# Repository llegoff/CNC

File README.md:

CNC
===

Fraiseuse à commande numérique
------------------------------

SmoothieBox
-----------

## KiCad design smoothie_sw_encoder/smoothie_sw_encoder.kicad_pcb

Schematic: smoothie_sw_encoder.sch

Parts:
P1: CONN_5
P2: CONN_2
S1: ENCODEUR_ROTATIF
SP1: SPEAKER
SW1: SW_PUSH

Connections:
unnamed: P1.3, SP1.1
unnamed: P1.4, S1.3
unnamed: P1.5, S1.2
unnamed: P1.2, S1.4
unnamed: P2.1, SW1.2
unnamed: P2.2 (PM), SW1.1
unnamed: P1.1, S1.1, S1.5, SP1.2

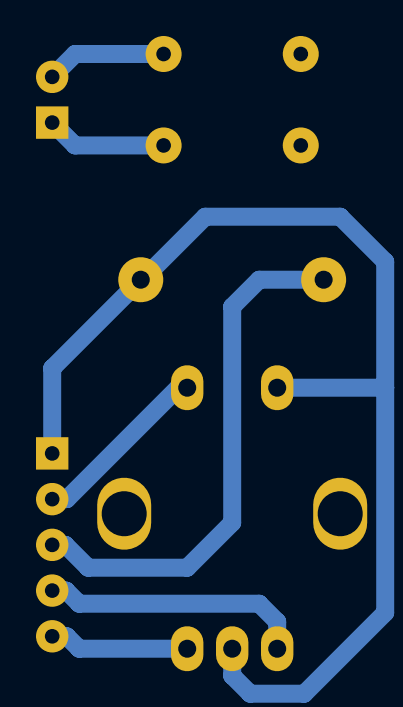
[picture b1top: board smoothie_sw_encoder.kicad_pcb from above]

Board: 2 copper layers, 5 parts (0 on the bottom side), 7 nets.

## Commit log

2014-01-16 1er téléversement
    1er téléversement
2014-05-15 smoothiebox
2014-05-16 smoothiebox scad
2014-05-25 pcb bouton play
2014-05-26 knob
